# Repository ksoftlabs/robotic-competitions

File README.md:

# robotic-competitions

This repo includes the codes of all the robots we made for competitions.

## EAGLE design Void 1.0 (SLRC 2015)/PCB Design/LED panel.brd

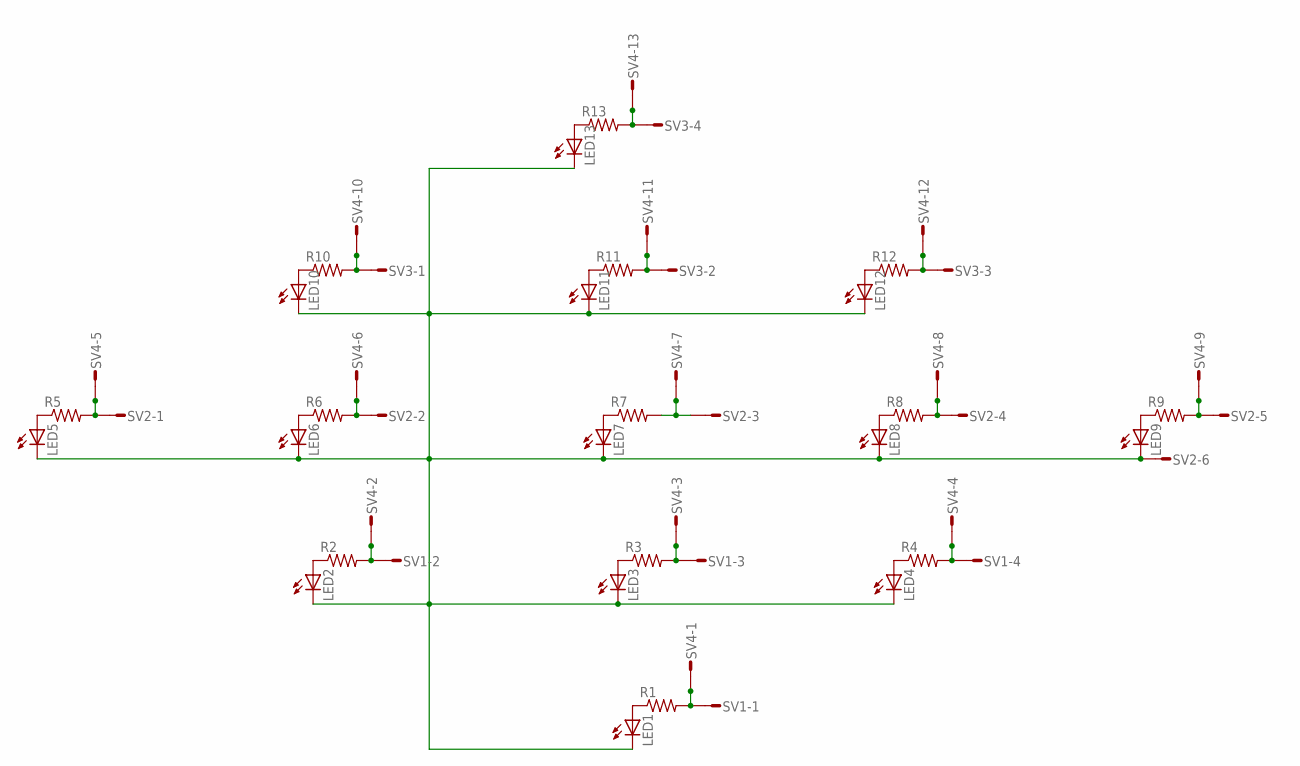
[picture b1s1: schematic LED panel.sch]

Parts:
LED1, LED2, LED3, LED4, LED5, LED6, LED7, LED8, LED9, LED10, LED11, LED12, LED13: LED5MM
R1, R2, R3, R4, R5, R6, R7, R8, R9, R10, R11, R12, R13: R-US_0204/5; 0204/5
SV1, SV3: L04P
SV2: L06P
SV4: L13P

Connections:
unnamed: LED1.A, R1.1
unnamed: LED2.A, R2.1
unnamed: LED1.K (C), LED2.K (C), LED3.K (C), LED4.K (C), LED5.K (C), LED6.K (C), LED7.K (C), LED8.K (C), LED9.K (C), LED10.K (C), LED11.K (C), LED12.K (C), LED13.K (C), SV2.6
unnamed: LED3.A, R3.1
unnamed: LED4.A, R4.1
unnamed: LED5.A, R5.1
unnamed: LED6.A, R6.1
unnamed: LED7.A, R7.1
unnamed: LED8.A, R8.1
unnamed: LED9.A, R9.1
unnamed: LED10.A, R10.1
unnamed: R11.2, SV3.2, SV4.11
unnamed: LED12.A, R12.1
unnamed: LED13.A, R13.1
unnamed: R13.2, SV3.4, SV4.13
unnamed: R10.2, SV3.1, SV4.10
unnamed: LED11.A, R11.1
unnamed: R12.2, SV3.3, SV4.12
unnamed: R9.2, SV2.5, SV4.9
unnamed: R8.2, SV2.4, SV4.8
unnamed: R7.2, SV2.3, SV4.7
unnamed: R6.2, SV2.2, SV4.6
unnamed: R5.2, SV2.1, SV4.5
unnamed: R2.2, SV1.2, SV4.2
unnamed: R3.2, SV1.3, SV4.3
unnamed: R4.2, SV1.4, SV4.4
unnamed: R1.2, SV1.1, SV4.1

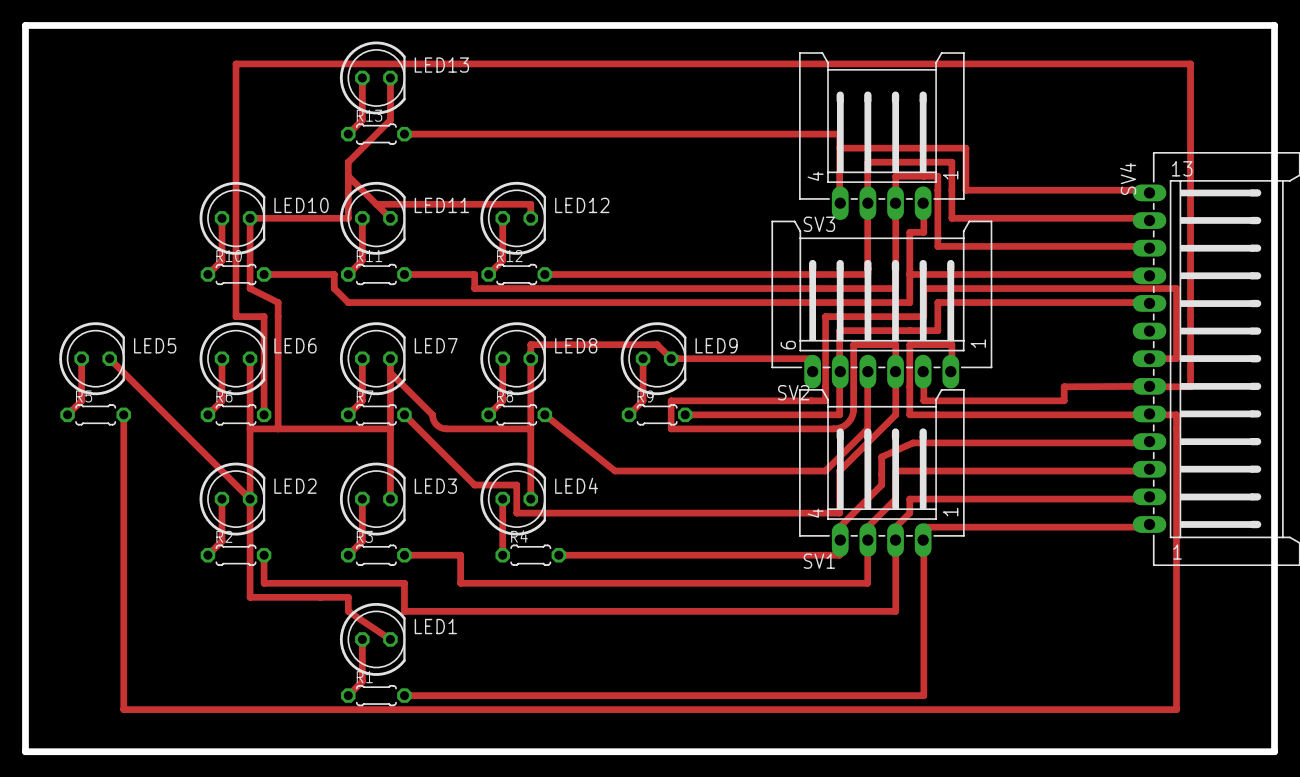
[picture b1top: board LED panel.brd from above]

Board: 2 copper layers, 113.0 x 65.7 mm, 30 parts (0 on the bottom side), 27 nets.

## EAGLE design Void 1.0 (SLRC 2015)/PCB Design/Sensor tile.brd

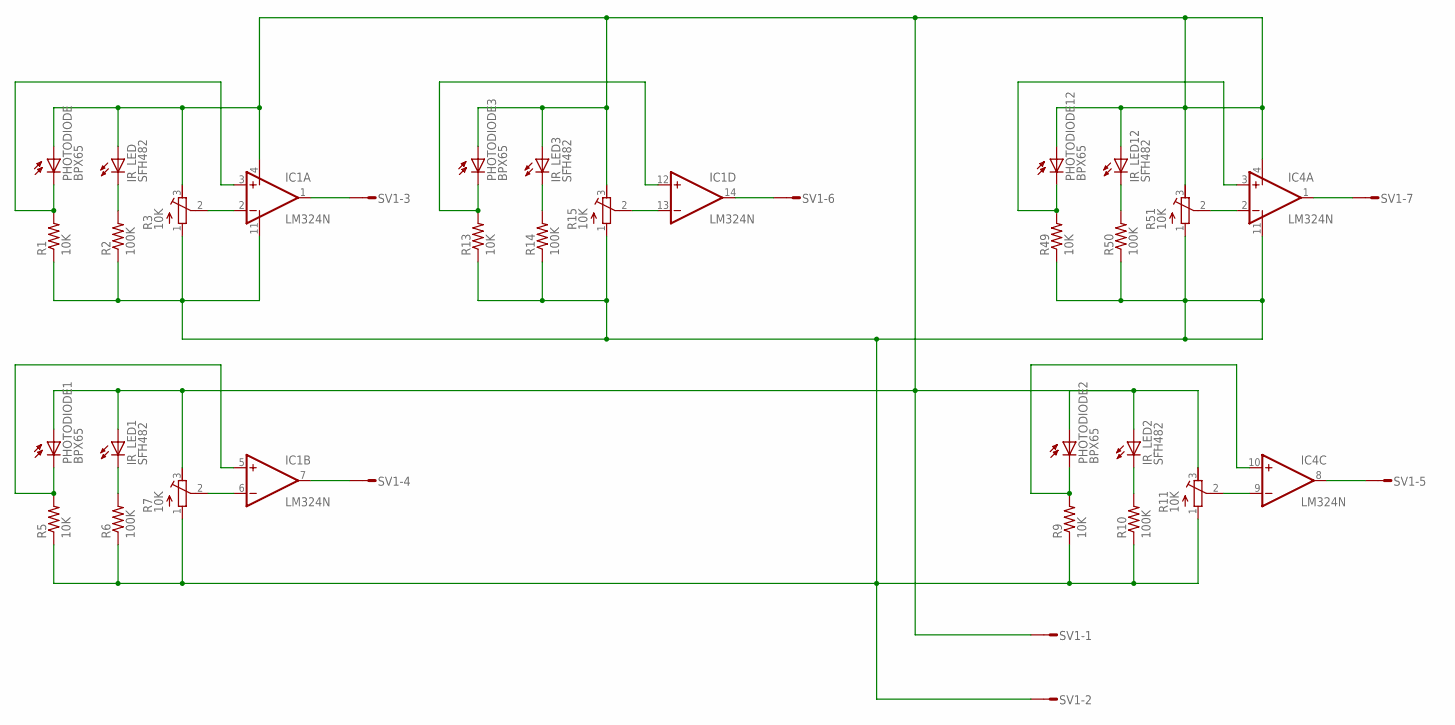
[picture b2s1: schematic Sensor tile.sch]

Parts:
IC1, IC4: LM324N; DIL14
IR_LED, IR_LED1, IR_LED2, IR_LED3, IR_LED12: SFH482
PHOTODIODE, PHOTODIODE1, PHOTODIODE2, PHOTODIODE3, PHOTODIODE12: BPX65
R1, R5, R9, R13, R49: 10K; 0204/7
R2, R6, R10, R14, R50: 100K; 0204/7
R3, R7, R11, R15, R51: 10K; RTRIM4G/J
SV1: L07P

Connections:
unnamed: IC1.3 (+IN), PHOTODIODE.K (C), R1.2
unnamed: IR_LED.K (C), R2.2
unnamed: IC1.2 (-IN), R3.2 (S)
unnamed: IC1.1 (OUT), SV1.3
unnamed: IC1.5 (+IN), PHOTODIODE1.K (C), R5.2
unnamed: IR_LED1.K (C), R6.2
unnamed: IC1.6 (-IN), R7.2 (S)
unnamed: IC1.7 (OUT), SV1.4
unnamed: IC1.4 (V+), IC4.4 (V+), IR_LED.A, IR_LED1.A, IR_LED2.A, IR_LED3.A, IR_LED12.A, PHOTODIODE.A, PHOTODIODE1.A, PHOTODIODE2.A, PHOTODIODE3.A, PHOTODIODE12.A, R3.3 (E), R7.3 (E), R11.3 (E), R15.3 (E), R51.3 (E), SV1.1
unnamed: IC4.10 (+IN), PHOTODIODE2.K (C), R9.2
unnamed: IR_LED2.K (C), R10.2
unnamed: IC1.11 (V-), IC4.11 (V-), R1.1, R2.1, R3.1 (A), R5.1, R6.1, R7.1 (A), R9.1, R10.1, R11.1 (A), R13.1, R14.1, R15.1 (A), R49.1, R50.1, R51.1 (A), SV1.2
unnamed: IC4.9 (-IN), R11.2 (S)
unnamed: IC4.8 (OUT), SV1.5
unnamed: IC1.12 (+IN), PHOTODIODE3.K (C), R13.2
unnamed: IR_LED3.K (C), R14.2
unnamed: IC1.13 (-IN), R15.2 (S)
unnamed: IC1.14 (OUT), SV1.6
unnamed: IC4.3 (+IN), PHOTODIODE12.K (C), R49.2
unnamed: IR_LED12.K (C), R50.2
unnamed: IC4.2 (-IN), R51.2 (S)
unnamed: IC4.1 (OUT), SV1.7

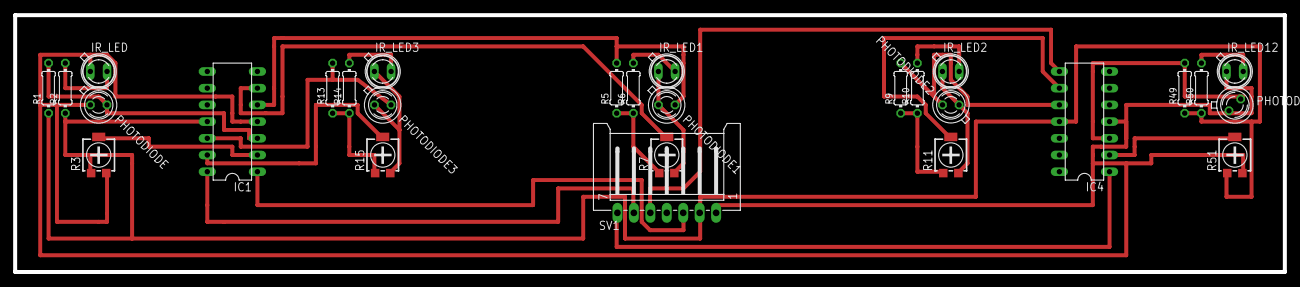
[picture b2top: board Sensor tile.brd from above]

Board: 2 copper layers, 193.0 x 39.0 mm, 28 parts (0 on the bottom side), 22 nets.

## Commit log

2016-07-31 no message
2016-07-31 modified waitKey(1) line for support in linux also
2016-08-04 Corrected an error. Now the project compiles fine.
2016-08-04 Included FPS, CPU usage, RAM usage to test efficiency
2016-08-05 Added support to use android cam
2016-08-05 robot = physics.Robot(comm, android=True) change android parameter to False to run from the laptop webcam
2016-08-06 FINALLY!!! Identified the head and the base!. Need momre optimizing
2016-08-06 chandeg physics.Robots to accept a new parameter ip ip = ip_address of your ip cam
2016-08-06 refined
2016-08-06 use IP Testing area/main.py for Image processing Testing arrow and rectangle detetction done by 2 fuctions in cmn.py, work on them if you can don't chnage anything else in cmn.py (pipline of it)
2016-08-06 methods! methods!! methods!!!
2016-08-06 change IP Testing pipine to filter more than one color range at once stated box detection function
2016-08-06 eaning trash
2016-08-06 Added Box detection
2016-08-07 Corrected
2016-08-07 Path queue added Beginig to form a solution to navigate by arrow heads
2016-08-07 Offset error calculation is done
2016-08-07 done!
2016-08-07 added box frame texts for testing
2016-08-09 Corrected errors
2016-08-09 fnished work on calibration.py added box_logic.py in IP Testing area
2016-08-10 added folder v1 to test box_logic with main loop made some changes to box_logic
2016-08-10 New Jython project
2016-08-10 Jython failed!
2016-08-10 Started adding gui
2016-08-10 NO GUI! NO WAY!! NOT IN PYTHON!!! NEVER!!!
2016-08-10 completed box detection
2016-08-10 (deleted old box file)
2016-08-25 Restructuring
